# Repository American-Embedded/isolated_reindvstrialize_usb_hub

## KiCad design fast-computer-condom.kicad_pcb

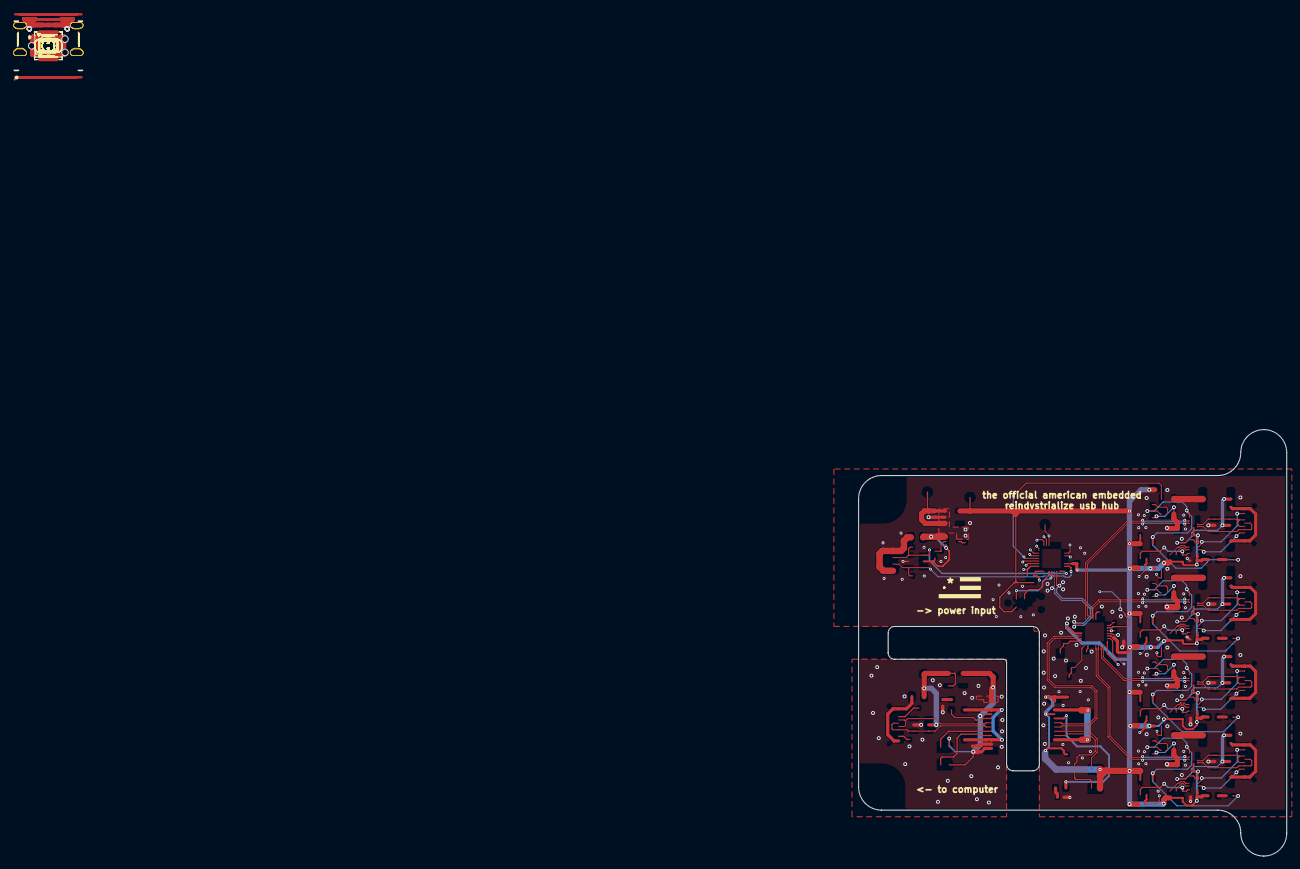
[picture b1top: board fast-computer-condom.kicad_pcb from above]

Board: 6 copper layers, 65.2 x 65.0 mm, 156 parts (0 on the bottom side), 107 nets.

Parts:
C2, C4, C5, C6, C7, C11, C12, C13, C14, C16, C17, C18, C19, C20, C22, C23, C53: 1uF; C_0402_1005Metric
C3, C10, C24, C44, C49: 4.7uF; C_0603_1608Metric
C15: 30pF; C_0402_1005Metric
C30, C32, C36, C39: 22uF; C_1206_3216Metric
C31, C35, C38, C41: 47uF; C_1206_3216Metric
C42, C45, C47, C50, C54, C60, C61, C62, C63, C64, C65, C66, C67: 100nF; C_0402_1005Metric
C43, C46, C48, C51, C52: 10nF; C_0402_1005Metric
D1, D2, D3, D4, D5, D6: GREEN; LED_0603_1608Metric
F1: 1A; Fuse_0805_2012Metric
F2: 3A; Fuse_0805_2012Metric
F3, F4, F5, F6: 750mA; Fuse_1812_4532Metric
H1, H2, H3, H4: MountingHole; MountingHole_2.2mm_M2_DIN965_Pad_TopBottom
J1: USB-C / HOST; USB_C_Receptacle_HRO_TYPE-C-31-M-12-Edge_Silkscreen_Removed
J2: USB-C / AUX POWER; USB_C_Receptacle_HRO_TYPE-C-31-M-17-No-Silkscreen
J3: Conn_ARM_SWD_TagConnect_TC2030-NL; Tag-Connect_TC2030-IDC-NL_2x03_P1.27mm_Vertical
J5, J7, J9, J11: USB-C / USB 2.0; USB_C_Receptacle_HRO_TYPE-C-31-M-12-Edge_Silkscreen_Removed
JP1, JP2, JP3, JP4: Jumper_3_Open; SolderJumper-3_P1.3mm_Bridged12_RoundedPad1.0x1.5mm
R1, R2, R28, R29, R38, R39: 5.1kR; R_0402_1005Metric
R3, R4, R30, R31, R32, R33: 1kR; R_0402_1005Metric
R5, R6, R7, R8, R40, R53, R54, R55, R56: 100kR; R_0402_1005Metric
R17: 6.8kR; R_0402_1005Metric
R18: 9.1kR; R_0402_1005Metric
R19: 4.7MR; R_0402_1005Metric
R20, R21, R22, R23, R24, R25, R26, R27: 51kR; R_0402_1005Metric
R41, R42, R43, R44, R45, R46, R47, R48, R49, R50, R51, R52: 10kR; R_0402_1005Metric
TP10, TP11, TP12, TP13, TP14, TP15, TP16: TestPoint; TestPoint_Pad_D1.5mm
U2, U6, U10, U13, U14, U15: USBLC6-2SC6; SOT-23-6
U3, U5: AP2112K-3.3; SOT-23-5
U4: CH32X035G8U6; WQFN-28-1EP_4x4mm_P0.4mm_EP2.7x2.7mm_ThermalVias
U7: CH338F; QFN-32-1EP_4x4mm_P0.4mm_EP2.65x2.65mm_ThermalVias
U8, U9, U11, U12: CH217A; SOT-23-6
U16: ISOUSB211DPR; SSOP-28_L10.3-W7.5-P0.65-LS10.3-BL
U20, U21, U22, U23: TS3USB221ERSER; UQFN-10_L2.0-W1.5-P0.50-BL-EP
U24: TPS22975NDSGR; WSON-8_L2.0-W2.0-P0.50-TL-EP
U25, U26, U27, U28: WUSB3801Q-12/TR; X2QFN-12_L1.6-W1.6-P0.40-LS1.2
U29, U30, U31, U32: SN74LVC1G32DBVR; SOT-23-5
Y2: 25M, 10pF; Crystal_SMD_3225-4Pin_3.2x2.5mm

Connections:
+3V3: C2.1, C4.1, C20.1, JP1.3 (B), JP2.3 (B), TP12.1 (1_1), U3.5 (VOUT), U16.1 (VBUS1), U16.2 (V3P3V1), U16.5 (VCC1), U16.13 (CDPENZ1)
+3V3_{ISO}: C7.1, C10.1, C11.1, C12.1, C16.1, C17.1, C18.1, C19.1, C22.1, C23.1, C60.1, C61.1, C62.1, C63.1, C64.1, C65.1, C66.1, C67.1, D3.2 (A), D4.2 (A), D5.2 (A), D6.2 (A), J3.1 (VCC), JP3.3 (B), JP4.3 (B), R20.1, R21.1, R22.1, R23.1, R24.1, R25.1, R26.1, R27.1, R28.1, R29.1, R41.1, R42.1, R43.1, R44.1, R45.1, R46.1, R47.1, R48.1, R49.1, R50.1, R51.1, R52.1, TP16.1 (1_1), U4.2 (VDD), U5.5 (VOUT), U7.5 (VDD33), U7.19 (VDD33), U16.16 (CDPENZ2), U16.24 (VCC2), U16.27 (V3P3V2), U16.28 (VBUS2), U20.10 (VCC), U21.10 (VCC), U22.10 (VCC), U23.10 (VCC), U25.3 (ROLE), U25.12 (VDD), U26.3 (ROLE), U26.12 (VDD), U27.3 (ROLE), U27.12 (VDD), U28.3 (ROLE), U28.12 (VDD), U29.5 (VCC), U30.5 (VCC), U31.5 (VCC), U32.5 (VCC)
/AUX_CC1: J2.A5 (CC1), R38.1, U4.28 (PC14/CC1), U6.1 (I/O1), U6.6 (I/O1)
/AUX_CC2: J2.B5 (CC2), R39.1, U4.1 (PC15/CC2), U6.3 (I/O2), U6.4 (I/O2)
/CTRL_D+: U4.27 (PC10/PC17/UDP), U7.2 (DP6)
/CTRL_D-: U4.26 (PC11/PC16/UDM), U7.1 (DM6)
/D+: J1.A6 (D+), J1.B6 (D+), U2.3 (I/O2), U2.4 (I/O2), U16.8 (UD+)
/D-: J1.A7 (D-), J1.B7 (D-), U2.1 (I/O1), U2.6 (I/O1), U16.7 (UD-)
/DD+: U7.7 (DPU+), U16.21 (DD+)
/DD-: U7.6 (DMU-), U16.22 (DD-)
/HUB_OC_N: U4.6 (PA1), U7.22 (~OVCUR)
/HUB_PWR_N: R17.1, U4.5 (PA0), U7.21 (~PWREN)
/INPUT_START: C54.1, R40.2, U24.3 (ON)
/SCL: R28.2, U4.21 (PB10), U7.18 (SMBCLK)
/SDA: R29.2, U4.22 (PB11), U7.17 (SMBDAT)
/SWCLK: J3.4 (SWCLK), U4.24 (PC19/DCK)
/SWDIO: J3.2 (SWDIO), U4.25 (PC18/DIO)
/USB_EN1: R24.2, U4.13 (PB0), U29.2
/USB_EN2: R26.2, U4.16 (PB1/PB5), U30.2
/USB_EN3: R27.2, U4.14 (PB3), U32.2
/USB_EN4: R25.2, U4.15 (PB4), U31.2
/USB_OVC1: R20.2, U4.17 (PB6), U8.3 (~FLAG)
/USB_OVC2: R22.2, U4.18 (PB7), U11.3 (~FLAG)
/USB_OVC3: R23.2, U4.19 (PB8), U12.3 (~FLAG)
/USB_OVC4: R21.2, U4.20 (PB9), U9.3 (~FLAG)
/USB_Output1/ATTACH_N: R43.2, U27.9 (ID), U31.1
/USB_Output1/D+: U7.14 (DP2), U21.7 (D-)
/USB_Output1/D-: U7.13 (DM2), U21.8 (D+)
/USB_Output1/LOCAL_D+: J7.A6 (D+), J7.B6 (D+), U13.1 (I/O1), U13.6 (I/O1), U21.2 (D1-)
/USB_Output1/LOCAL_D-: J7.A7 (D-), J7.B7 (D-), U13.3 (I/O2), U13.4 (I/O2), U21.1 (D1+)
/USB_Output1/PORT_CC1: J7.A5 (CC1), U27.1 (CC1)
/USB_Output1/PORT_CC2: J7.B5 (CC2), U27.2 (CC2)
/USB_Output1/PORT_DISABLE: R31.2, R55.2, U9.4 (~EN), U21.6 (~OE), U31.4
/USB_Output1/PORT_VBUS: C35.1, F4.2, J7.A4 (VBUS), J7.A9 (VBUS), J7.B4 (VBUS), J7.B9 (VBUS), U13.5 (VBUS), U27.4 (VBUSD)
/USB_Output2/ATTACH_N: R42.2, U26.9 (ID), U30.1
/USB_Output2/D+: U7.32 (DP3), U22.7 (D-)
/USB_Output2/D-: U7.31 (DM3), U22.8 (D+)
/USB_Output2/LOCAL_D+: J9.A6 (D+), J9.B6 (D+), U14.1 (I/O1), U14.6 (I/O1), U22.2 (D1-)
/USB_Output2/LOCAL_D-: J9.A7 (D-), J9.B7 (D-), U14.3 (I/O2), U14.4 (I/O2), U22.1 (D1+)
/USB_Output2/PORT_CC1: J9.A5 (CC1), U26.1 (CC1)
/USB_Output2/PORT_CC2: J9.B5 (CC2), U26.2 (CC2)
/USB_Output2/PORT_DISABLE: R32.2, R54.2, U11.4 (~EN), U22.6 (~OE), U30.4
/USB_Output2/PORT_VBUS: C38.1, F5.2, J9.A4 (VBUS), J9.A9 (VBUS), J9.B4 (VBUS), J9.B9 (VBUS), U14.5 (VBUS), U26.4 (VBUSD)
/USB_Output3/ATTACH_N: R44.2, U28.9 (ID), U32.1
/USB_Output3/D+: U7.16 (DP5), U23.7 (D-)
/USB_Output3/D-: U7.15 (DM5), U23.8 (D+)
/USB_Output3/LOCAL_D+: J11.A6 (D+), J11.B6 (D+), U15.1 (I/O1), U15.6 (I/O1), U23.2 (D1-)
/USB_Output3/LOCAL_D-: J11.A7 (D-), J11.B7 (D-), U15.3 (I/O2), U15.4 (I/O2), U23.1 (D1+)
/USB_Output3/PORT_CC1: J11.A5 (CC1), U28.1 (CC1)
/USB_Output3/PORT_CC2: J11.B5 (CC2), U28.2 (CC2)
/USB_Output3/PORT_DISABLE: R33.2, R56.2, U12.4 (~EN), U23.6 (~OE), U32.4
/USB_Output3/PORT_VBUS: C41.1, F6.2, J11.A4 (VBUS), J11.A9 (VBUS), J11.B4 (VBUS), J11.B9 (VBUS), U15.5 (VBUS), U28.4 (VBUSD)
/USB_Output/ATTACH_N: R41.2, U25.9 (ID), U29.1
/USB_Output/D+: U7.30 (DP4), U20.7 (D-)
/USB_Output/D-: U7.29 (DM4), U20.8 (D+)
/USB_Output/LOCAL_D+: J5.A6 (D+), J5.B6 (D+), U10.1 (I/O1), U10.6 (I/O1), U20.2 (D1-)
/USB_Output/LOCAL_D-: J5.A7 (D-), J5.B7 (D-), U10.3 (I/O2), U10.4 (I/O2), U20.1 (D1+)
/USB_Output/PORT_CC1: J5.A5 (CC1), U25.1 (CC1)
/USB_Output/PORT_CC2: J5.B5 (CC2), U25.2 (CC2)
/USB_Output/PORT_DISABLE: R30.2, R53.2, U8.4 (~EN), U20.6 (~OE), U29.4
/USB_Output/PORT_VBUS: C31.1, F3.2, J5.A4 (VBUS), J5.A9 (VBUS), J5.B4 (VBUS), J5.B9 (VBUS), U10.5 (VBUS), U25.4 (VBUSD)
/V1P8_HOST: C3.1, C42.1, C43.1, C44.1, C45.1, C46.1, U16.4 (V1P8V1), U16.11 (V1P8V1)
/V1P8_ISO: C24.1, C47.1, C48.1, C49.1, C50.1, C51.1, U16.18 (V1P8V2), U16.25 (V1P8V2)
/~RESET.HUB: TP10.1 (1_1), U4.12 (PA7), U7.20 (~RESET)
GND: C2.2, C3.2, C4.2, C5.2, C20.2, C42.2, C43.2, C44.2, C45.2, C46.2, J1.A1 (GND), J1.A12 (GND), J1.B1 (GND), J1.B12 (GND), J1.SH (SHIELD), JP1.1 (A), JP2.1 (A), R1.2, R2.2, R3.2, TP13.1 (1_1), U2.2 (GND), U3.2 (GND), U16.3 (GND1), U16.12 (GND1)
GND2: C6.2, C7.2, C10.2, C11.2, C12.2, C13.2, C14.2, C15.2, C16.2, C17.2, C18.2, C19.2, C22.2, C23.2, C24.2, C30.2, C31.2, C32.2, C35.2, C36.2, C38.2, C39.2, C41.2, C47.2, C48.2, C49.2, C50.2, C51.2, C52.2, C53.2, C54.2, C60.2, C61.2, C62.2, C63.2, C64.2, C65.2, C66.2, C67.2, J2.A12 (GND), J2.B12 (GND), J2.SH (SHIELD), J3.5 (GND), J5.A1 (GND), J5.A12 (GND), J5.B1 (GND), J5.B12 (GND), J5.SH (SHIELD), J7.A1 (GND), J7.A12 (GND), J7.B1 (GND), J7.B12 (GND), J7.SH (SHIELD), J9.A1 (GND), J9.A12 (GND), J9.B1 (GND), J9.B12 (GND), J9.SH (SHIELD), J11.A1 (GND), J11.A12 (GND), J11.B1 (GND), J11.B12 (GND), J11.SH (SHIELD), JP3.1 (A), JP4.1 (A), R4.2, R5.2, R6.2, R7.2, R8.2, R17.2, R18.2, R19.2, R38.2, R39.2, TP15.1 (1_1), U4.29 (GND), U5.2 (GND), U6.2 (GND), U7.33 (GND), U8.2 (GND), U9.2 (GND), U10.2 (GND), U11.2 (GND), U12.2 (GND), U13.2 (GND), U14.2 (GND), U15.2 (GND), U16.17 (GND2), U16.26 (GND2), U20.5 (GND), U20.9 (S), U21.5 (GND), U21.9 (S), U22.5 (GND), U22.9 (S), U23.5 (GND), U23.9 (S), U24.5 (GND), U24.9 (EP), U25.10 (GND), U25.11 (ENB), U26.10 (GND), U26.11 (ENB), U27.10 (GND), U27.11 (ENB), U28.10 (GND), U28.11 (ENB), U29.3 (GND), U30.3 (GND), U31.3 (GND), U32.3 (GND), Y2.2 (G), Y2.4 (G)
unnamed: D1.2 (A), U16.6 (V2OK)
unnamed: D1.1 (K), R3.1
unnamed: D2.2 (A), U16.23 (V1OK)
unnamed: D2.1 (K), R4.1
unnamed: D3.1 (K), R30.1
unnamed: D4.1 (K), R31.1
unnamed: D5.1 (K), R32.1
unnamed: D6.1 (K), R33.1
unnamed: F1.1, J1.A4 (VBUS), J1.A9 (VBUS), J1.B4 (VBUS), J1.B9 (VBUS)
unnamed: F2.1, J2.A9 (VBUS), J2.B9 (VBUS)
unnamed: J1.A5 (CC1), R2.1
unnamed: J1.B5 (CC2), R1.1
unnamed: JP1.2 (C), U16.9 (EQ10)
unnamed: JP2.2 (C), U16.10 (EQ11)
unnamed: JP3.2 (C), U16.20 (EQ20)
unnamed: JP4.2 (C), U16.19 (EQ21)
unnamed: C5.1, F1.2, TP11.1 (1_1), U2.5 (VBUS), U3.1 (VIN), U3.3 (EN)
unnamed: C13.1, U7.10 (AVDDK)
unnamed: R18.1, U7.23 (CFG)
unnamed: C14.1, U7.28 (DVDDK)
unnamed: R19.1, U7.9 (XI), Y2.1
unnamed: C15.1, U7.8 (XO), Y2.3
unnamed: R5.1, U8.5 (ISET)
unnamed: F3.1, U8.1 (VOUT)
unnamed: R6.1, U9.5 (ISET)
unnamed: F4.1, U9.1 (VOUT)
unnamed: R7.1, U11.5 (ISET)
unnamed: F5.1, U11.1 (VOUT)
unnamed: R8.1, U12.5 (ISET)
unnamed: F6.1, U12.1 (VOUT)
unnamed: C52.1, U24.6 (CT)
unnamed: R49.2, U25.8 (SCL/INOUT2)
unnamed: R45.2, U25.7 (SDA/INOUT1)
unnamed: R50.2, U26.8 (SCL/INOUT2)
unnamed: R46.2, U26.7 (SDA/INOUT1)
unnamed: R51.2, U27.8 (SCL/INOUT2)
unnamed: R47.2, U27.7 (SDA/INOUT1)
unnamed: R52.2, U28.8 (SCL/INOUT2)
unnamed: R48.2, U28.7 (SDA/INOUT1)
VBUS_ISO_RAW: C53.1, F2.2, R40.1, U6.5 (VBUS), U24.1 (VIN), U24.2 (VIN), U24.4 (VBIAS)
VBUS_{ISO}: C6.1, C30.1, C32.1, C36.1, C39.1, R53.1, R54.1, R55.1, R56.1, TP14.1 (1_1), U5.1 (VIN), U5.3 (EN), U8.6 (VIN), U9.6 (VIN), U11.6 (VIN), U12.6 (VIN), U24.7 (VOUT), U24.8 (VOUT)
